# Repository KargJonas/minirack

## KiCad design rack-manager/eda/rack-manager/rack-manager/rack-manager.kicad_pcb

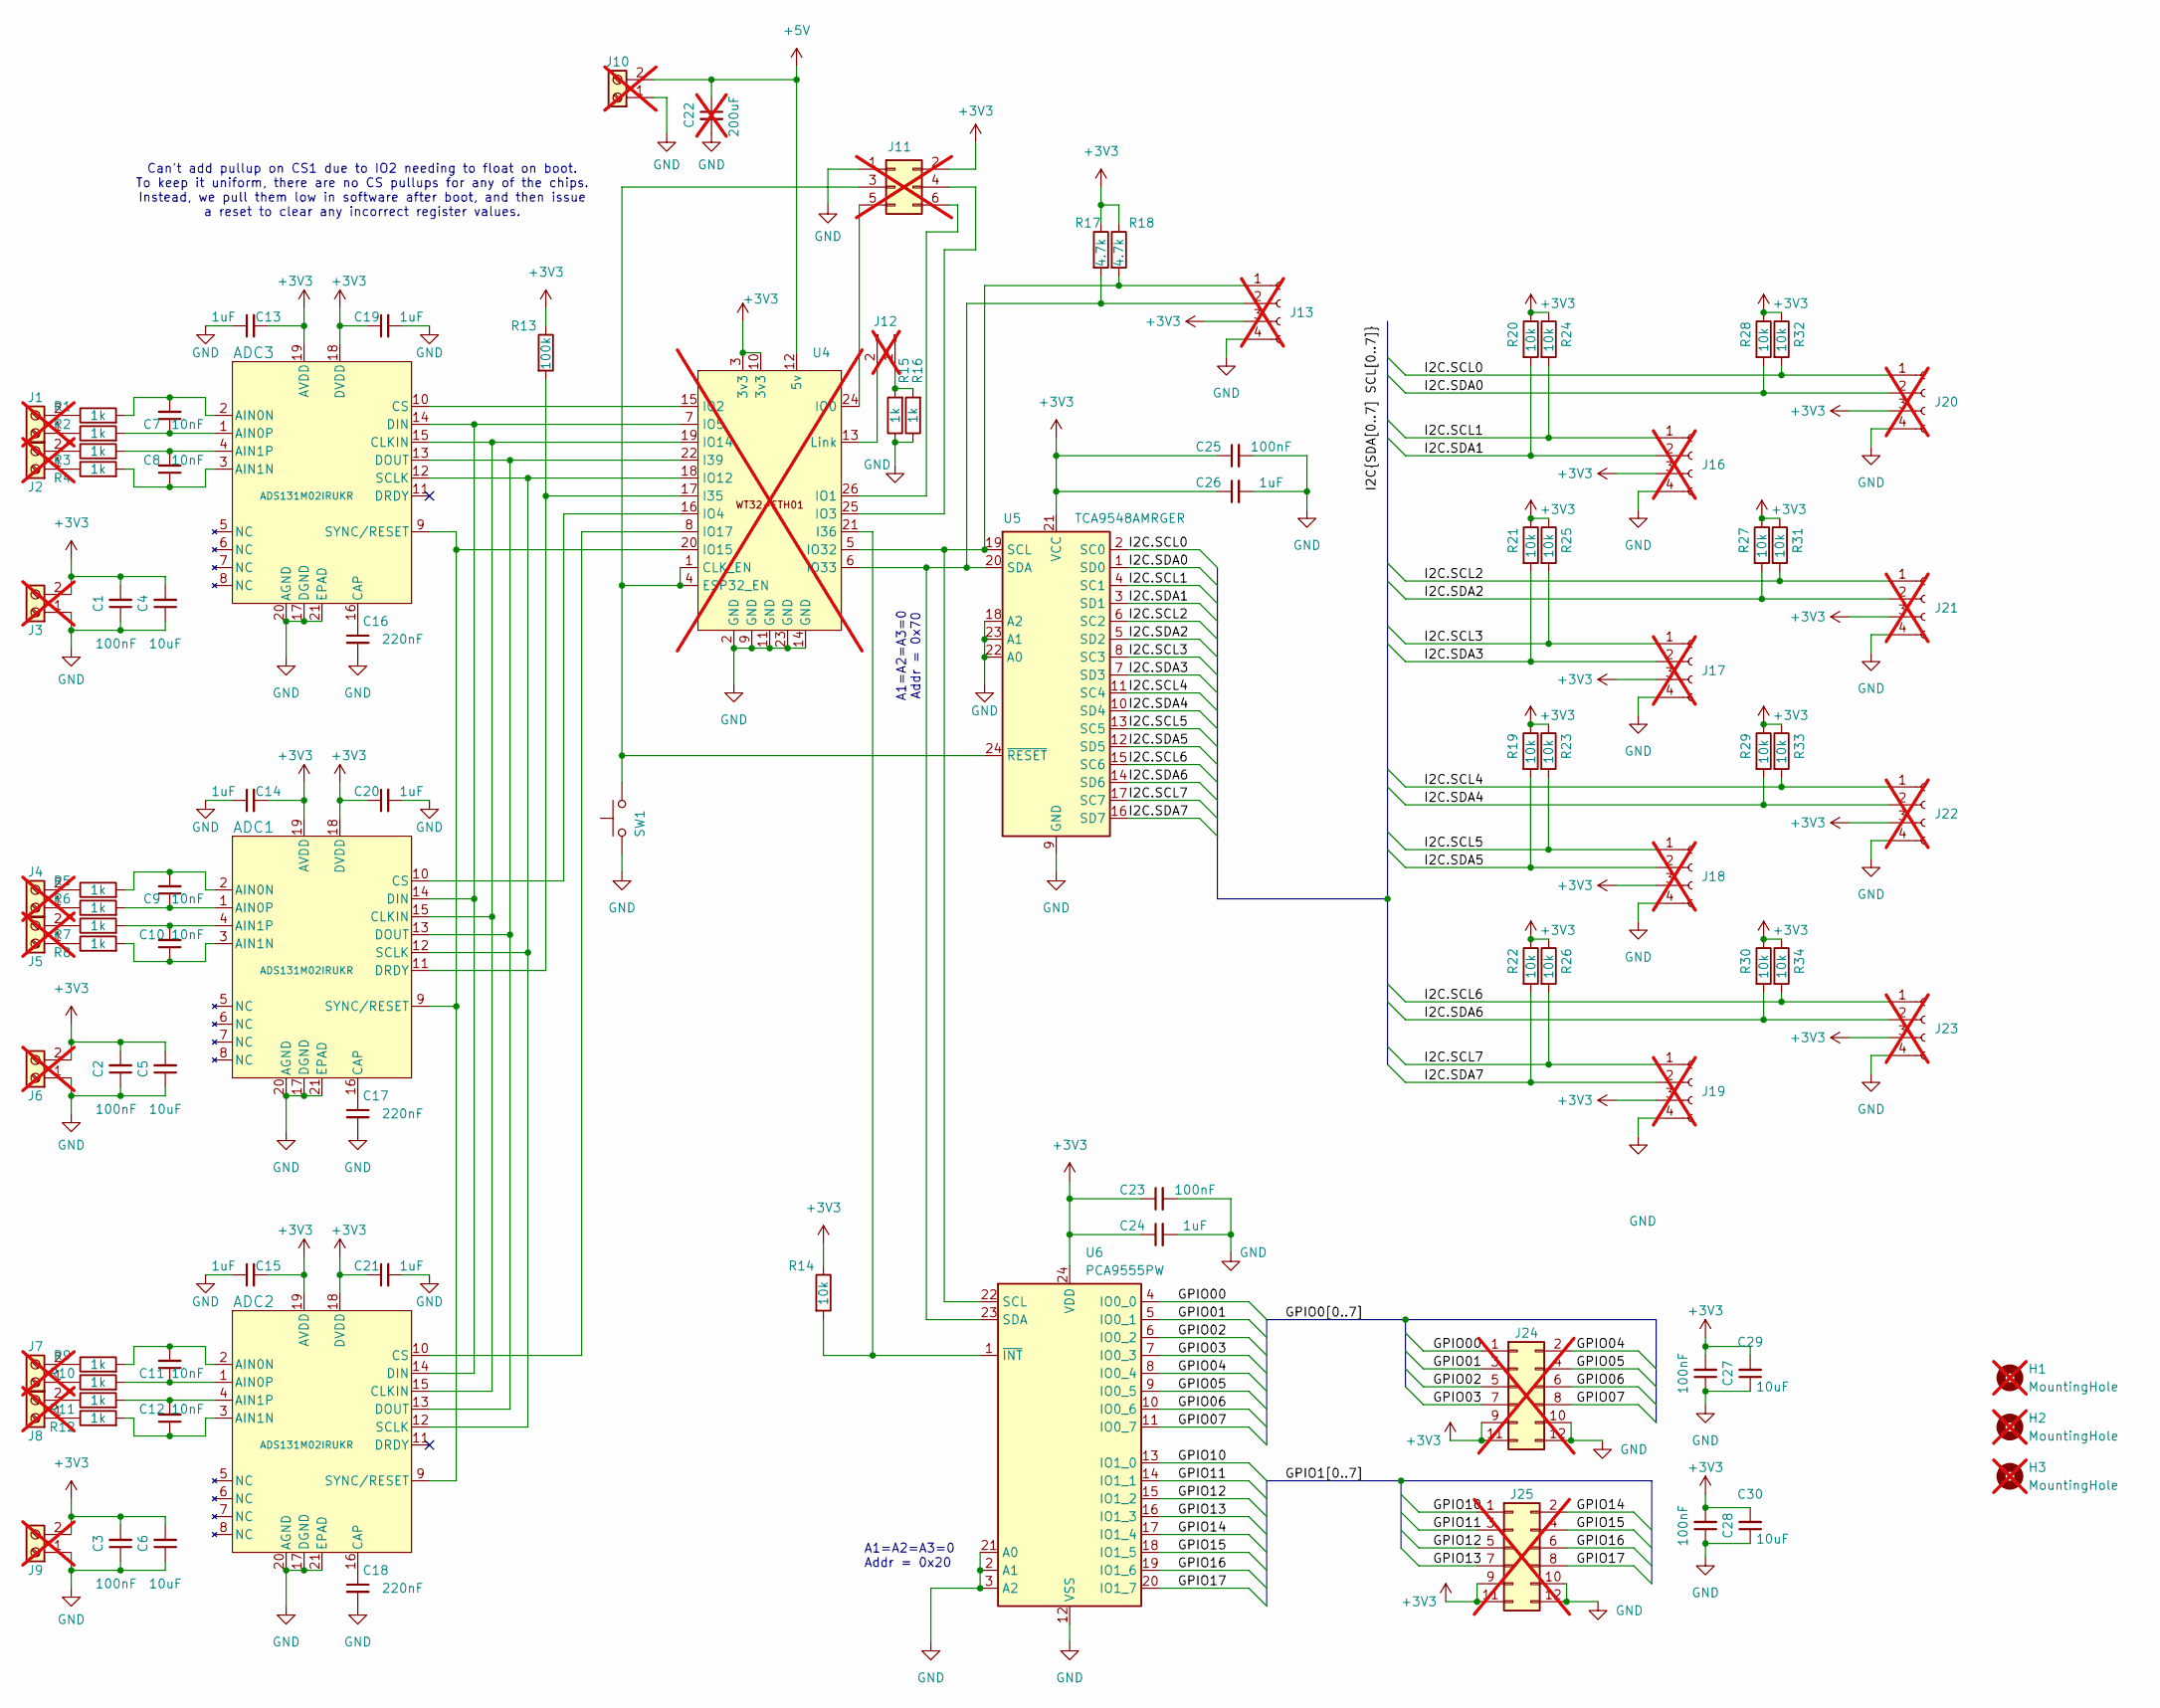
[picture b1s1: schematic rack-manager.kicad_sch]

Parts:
ADC1, ADC2, ADC3: ADS131M02IRUKR; WQFN-20-1EP_3x3mm_P0.4mm_EP1.7x1.7mm; LCSC C5215160
C1, C2, C3, C23, C25, C27, C28: 100nF; C_0603_1608Metric; LCSC C14663
C4, C5, C6, C29, C30: 10uF; C_0603_1608Metric; LCSC C19702
C7, C8, C9, C10, C11, C12: 10nF; C_0603_1608Metric; LCSC C57112
C13, C14, C15, C19, C20, C21, C24, C26: 1uF; C_0603_1608Metric; LCSC C15849
C16, C17, C18: 220nF; C_0603_1608Metric; LCSC C21120
C22: 200uF; CP_Radial_D8.0mm_P3.50mm; not fitted
H1, H2, H3: MountingHole; MountingHole_4.3mm_M4_ISO14580_Pad_TopBottom; not fitted
J1, J2, J3, J4, J5, J6, J7, J8, J9, J10: Screw_Terminal_01x02; TerminalBlock_Phoenix_MKDS-1-2-3.81_1x02_P3.81mm_Horizontal; not fitted
J11: Conn_02x03_Odd_Even; IDC-Header_2x03_P2.54mm_Vertical; not fitted
J12: Conn_01x02_Pin; PinHeader_1x02_P2.54mm_Vertical; not fitted
J13, J16, J17, J18, J19, J20, J21, J22, J23: Conn_01x04_Socket; JST_XH_B4B-XH-A_1x04_P2.50mm_Vertical; not fitted
J24, J25: Conn_02x06_Odd_Even; IDC-Header_2x06_P2.54mm_Vertical; not fitted
R1, R2, R3, R4, R5, R6, R7, R8, R9, R10, R11, R12, R15, R16: 1k; R_0603_1608Metric; LCSC C21190
R13: 100k; R_0603_1608Metric; LCSC C25803
R14, R19, R20, R21, R22, R23, R24, R25, R26, R27, R28, R29, R30, R31, R32, R33, R34: 10k; R_0603_1608Metric; LCSC C25804
R17, R18: 4.7k; R_0603_1608Metric; LCSC C23162
SW1: C720477; SW_Push_SPST_NO_Alps_SKRK; LCSC C720477
U4: WT32-ETH01; not fitted
U5: TCA9548AMRGER; Texas_RGE0024C_VQFN-24-1EP_4x4mm_P0.5mm_EP2.1x2.1mm
U6: PCA9555PW; TSSOP-24_4.4x7.8mm_P0.65mm

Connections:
+3V3: ADC1.18 (DVDD), ADC1.19 (AVDD), ADC2.18 (DVDD), ADC2.19 (AVDD), ADC3.18 (DVDD), ADC3.19 (AVDD), C1.2, C2.2, C3.2, C4.2, C5.2, C6.2, C13.2, C14.2, C15.2, C19.1, C20.1, C21.1, C23.1, C24.1, C25.1, C26.1, C27.2, C28.2, C29.2, C30.2, J3.2, J6.2, J9.2, J11.2, J13.3, J16.3, J17.3, J18.3, J19.3, J20.3, J21.3, J22.3, J23.3, J24.9, J24.11, J25.9, J25.11, R13.1, R14.1, R17.1, R18.1, R19.1, R20.1, R21.1, R22.1, R23.1, R24.1, R25.1, R26.1, R27.1, R28.1, R29.1, R30.1, R31.1, R32.1, R33.1, R34.1, U4.3 (3v3), U4.10 (3v3), U5.21 (VCC), U6.24 (VDD)
+5V: C22.1, J10.2, U4.12 (5v)
/GPIO00: J24.1, U6.4 (IO0_0)
/GPIO01: J24.3, U6.5 (IO0_1)
/GPIO02: J24.5, U6.6 (IO0_2)
/GPIO03: J24.7, U6.7 (IO0_3)
/GPIO04: J24.2, U6.8 (IO0_4)
/GPIO05: J24.4, U6.9 (IO0_5)
/GPIO06: J24.6, U6.10 (IO0_6)
/GPIO07: J24.8, U6.11 (IO0_7)
/GPIO10: J25.1, U6.13 (IO1_0)
/GPIO11: J25.3, U6.14 (IO1_1)
/GPIO12: J25.5, U6.15 (IO1_2)
/GPIO13: J25.7, U6.16 (IO1_3)
/GPIO14: J25.2, U6.17 (IO1_4)
/GPIO15: J25.4, U6.18 (IO1_5)
/GPIO16: J25.6, U6.19 (IO1_6)
/GPIO17: J25.8, U6.20 (IO1_7)
/I2C.SCL0: J20.1, R32.2, U5.2 (SC0)
/I2C.SCL1: J16.1, R24.2, U5.4 (SC1)
/I2C.SCL2: J21.1, R31.2, U5.6 (SC2)
/I2C.SCL3: J17.1, R25.2, U5.8 (SC3)
/I2C.SCL4: J22.1, R33.2, U5.11 (SC4)
/I2C.SCL5: J18.1, R23.2, U5.13 (SC5)
/I2C.SCL6: J23.1, R34.2, U5.15 (SC6)
/I2C.SCL7: J19.1, R26.2, U5.17 (SC7)
/I2C.SDA0: J20.2, R28.2, U5.1 (SD0)
/I2C.SDA1: J16.2, R20.2, U5.3 (SD1)
/I2C.SDA2: J21.2, R27.2, U5.5 (SD2)
/I2C.SDA3: J17.2, R21.2, U5.7 (SD3)
/I2C.SDA4: J22.2, R29.2, U5.10 (SD4)
/I2C.SDA5: J18.2, R19.2, U5.12 (SD5)
/I2C.SDA6: J23.2, R30.2, U5.14 (SD6)
/I2C.SDA7: J19.2, R22.2, U5.16 (SD7)
GND: ADC1.17 (DGND), ADC1.20 (AGND), ADC1.21 (EPAD), ADC2.17 (DGND), ADC2.20 (AGND), ADC2.21 (EPAD), ADC3.17 (DGND), ADC3.20 (AGND), ADC3.21 (EPAD), C1.1, C2.1, C3.1, C4.1, C5.1, C6.1, C13.1, C14.1, C15.1, C16.2, C17.2, C18.2, C19.2, C20.2, C21.2, C22.2, C23.2, C24.2, C25.2, C26.2, C27.1, C28.1, C29.1, C30.1, J3.1, J6.1, J9.1, J10.1, J11.1, J13.4, J16.4, J17.4, J18.4, J19.4, J20.4, J21.4, J22.4, J23.4, J24.10, J24.12, J25.10, J25.12, R15.1, R16.1, SW1.1, U4.2 (GND), U4.9 (GND), U4.11 (GND), U4.14 (GND), U4.23 (GND), U5.9 (GND), U5.18 (A2), U5.22 (A0), U5.23 (A1), U6.2 (A1), U6.3 (A2), U6.12 (VSS), U6.21 (A0)
unnamed: ADC1.2 (AIN0N), C9.2, R5.2
unnamed: ADC1.1 (AIN0P), C9.1, R6.2
unnamed: ADC1.3 (AIN1N), C10.1, R8.2
unnamed: ADC1.4 (AIN1P), C10.2, R7.2
unnamed: ADC1.16 (CAP), C17.1
unnamed: ADC1.15 (CLKIN), ADC2.15 (CLKIN), ADC3.15 (CLKIN), U4.19 (IO14)
unnamed: ADC1.10 (CS), U4.16 (IO4)
unnamed: ADC1.14 (DIN), ADC2.14 (DIN), ADC3.14 (DIN), U4.7 (IO5)
unnamed: ADC1.13 (DOUT), ADC2.13 (DOUT), ADC3.13 (DOUT), U4.22 (I39)
unnamed: ADC1.11 (DRDY), R13.2, U4.17 (I35)
unnamed: ADC1.12 (SCLK), ADC2.12 (SCLK), ADC3.12 (SCLK), U4.18 (IO12)
unnamed: ADC1.9 (SYNC/RESET), ADC2.9 (SYNC/RESET), ADC3.9 (SYNC/RESET), U4.20 (IO15)
unnamed: ADC2.2 (AIN0N), C11.2, R9.2
unnamed: ADC2.1 (AIN0P), C11.1, R10.2
unnamed: ADC2.3 (AIN1N), C12.1, R12.2
unnamed: ADC2.4 (AIN1P), C12.2, R11.2
unnamed: ADC2.16 (CAP), C18.1
unnamed: ADC2.10 (CS), U4.8 (IO17)
unnamed: ADC3.2 (AIN0N), C7.2, R1.2
unnamed: ADC3.1 (AIN0P), C7.1, R2.2
unnamed: ADC3.3 (AIN1N), C8.1, R4.2
unnamed: ADC3.4 (AIN1P), C8.2, R3.2
unnamed: ADC3.16 (CAP), C16.1
unnamed: ADC3.10 (CS), U4.15 (IO2)
unnamed: J1.1, R2.1
unnamed: J1.2, R1.1
unnamed: J2.1, R4.1
unnamed: J2.2, R3.1
unnamed: J4.1, R6.1
unnamed: J4.2, R5.1
unnamed: J5.1, R8.1
unnamed: J5.2, R7.1
unnamed: J7.1, R10.1
unnamed: J7.2, R9.1
unnamed: J8.1, R12.1
unnamed: J8.2, R11.1
unnamed: J11.3, SW1.2, U4.1 (CLK_EN), U4.4 (ESP32_EN), U5.24 (~RESET)
unnamed: J11.4, U4.25 (IO3)
unnamed: J11.5, U4.24 (IO0)
unnamed: J11.6, U4.26 (IO1)
unnamed: J12.1, R15.2, R16.2
unnamed: J12.2, U4.13 (Link)
unnamed: J13.1, R18.2, U4.5 (IO32), U5.19 (SCL), U6.22 (SCL)
unnamed: J13.2, R17.2, U4.6 (IO33), U5.20 (SDA), U6.23 (SDA)
unnamed: R14.2, U4.21 (I36), U6.1 (~INT)

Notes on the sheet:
Can't add pullup on CS1 due to IO2 needing to float on boot. To keep it uniform, there are no CS pullups for any of the chips. Instead, we pull them low in software after boot, and then issue a reset to clear any incorrect register values.
A1=A2=A3=0 Addr = 0x20
A1=A2=A3=0 Addr = 0x70

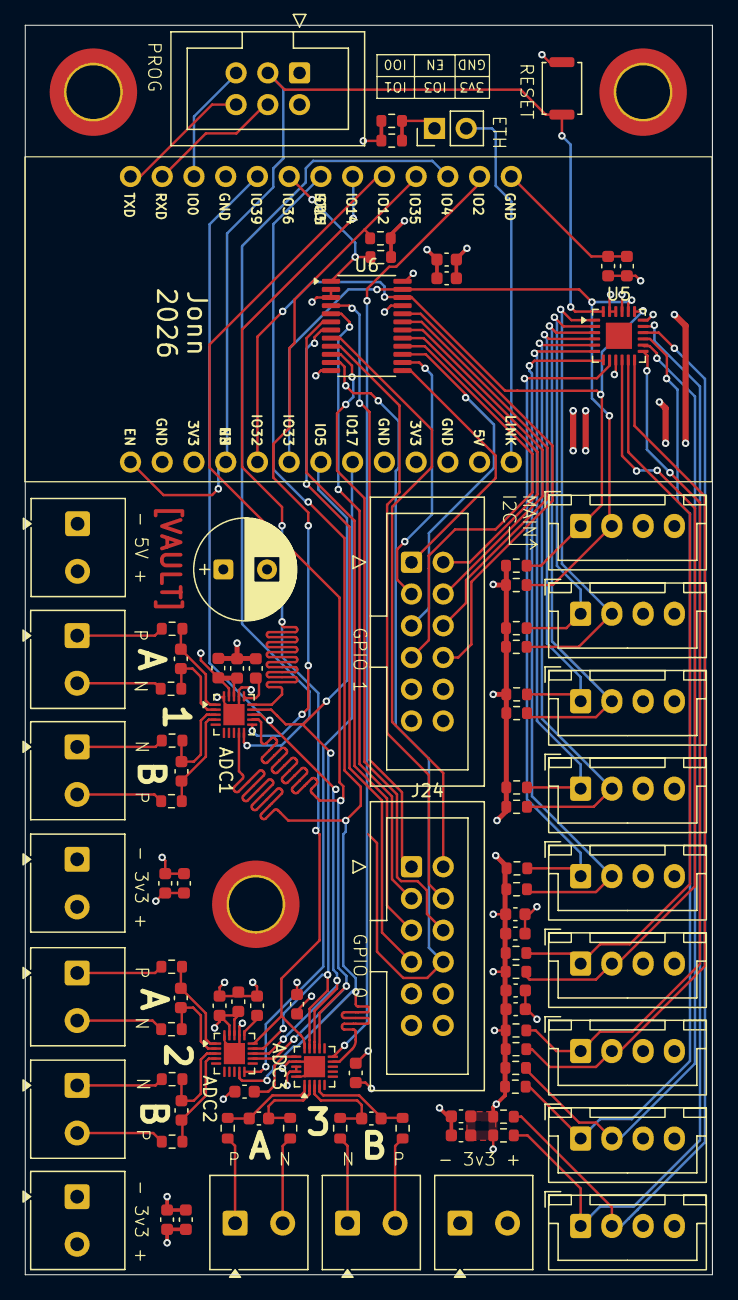
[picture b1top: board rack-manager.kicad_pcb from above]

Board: 4 copper layers, 55.0 x 100.0 mm, 97 parts (0 on the bottom side), 80 nets.
